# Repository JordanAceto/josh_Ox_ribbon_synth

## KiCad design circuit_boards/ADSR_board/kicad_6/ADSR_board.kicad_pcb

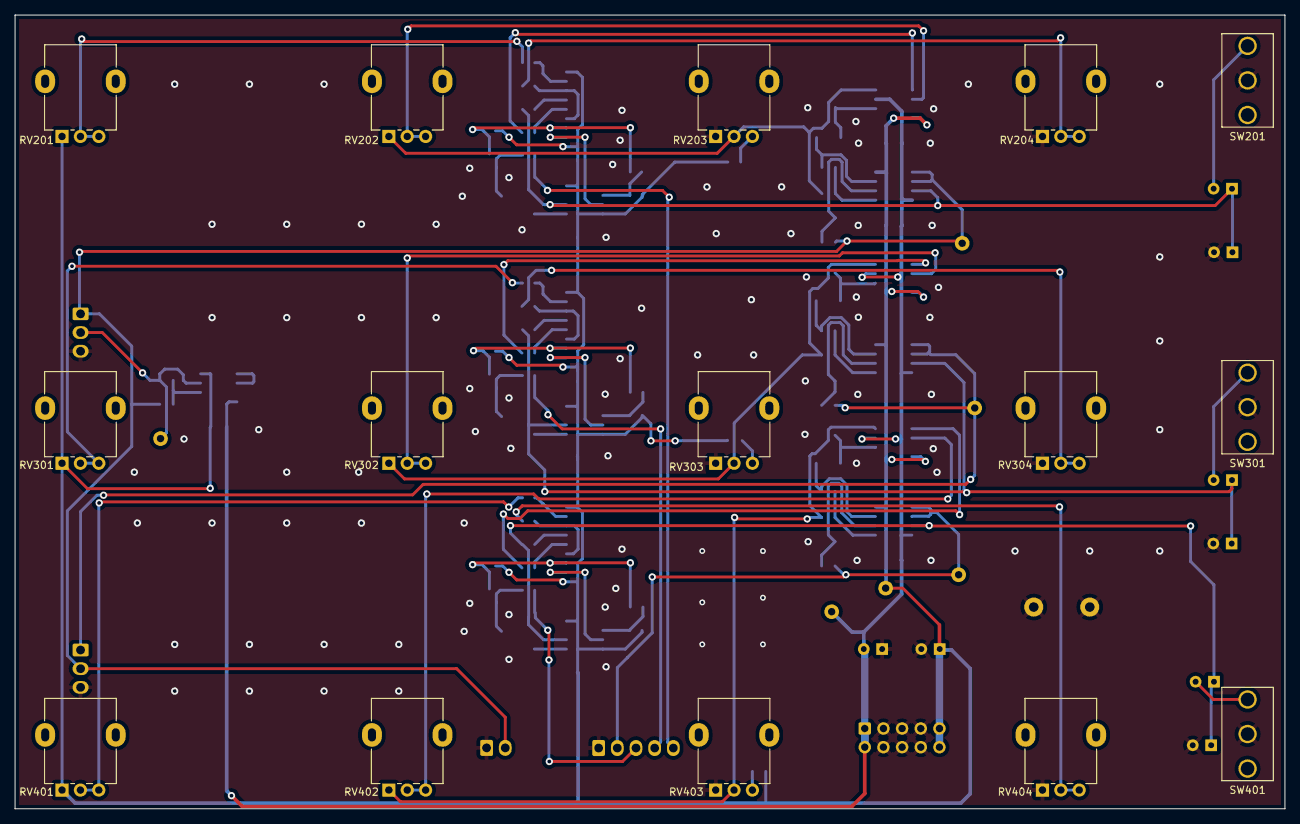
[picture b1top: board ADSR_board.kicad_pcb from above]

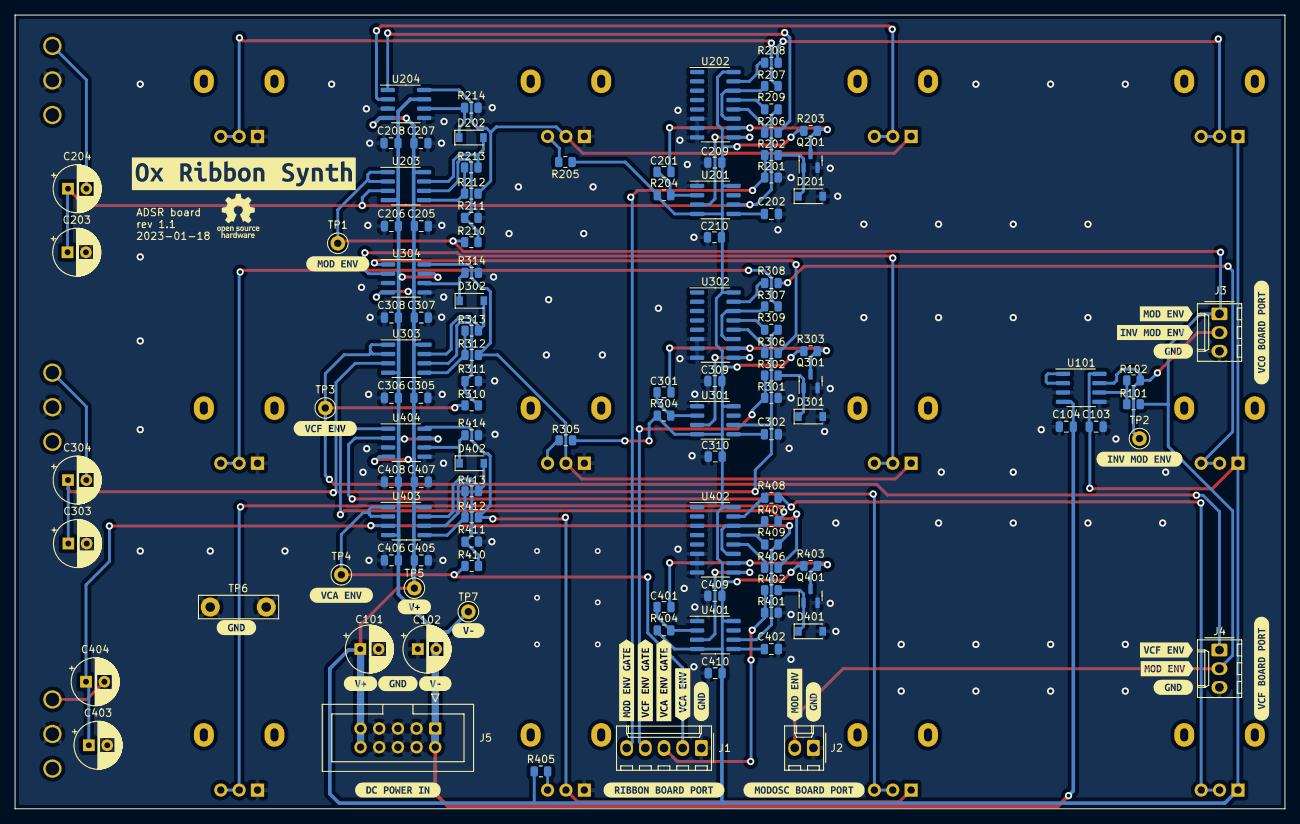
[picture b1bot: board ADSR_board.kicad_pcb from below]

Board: 2 copper layers, 172.7 x 107.9 mm, 156 parts (141 on the bottom side), 75 nets.

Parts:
C101, C102: 10u; CP_Radial_D6.3mm_P2.50mm
C103, C104, C205, C206, C207, C208, C209, C210, C305, C306, C307, C308, C309, C310, C405, C406, C407, C408, C409, C410: 100n; C_0805_2012Metric
C201, C202, C301, C302, C401, C402: 1n; C_0805_2012Metric
C203, C303, C403: 2u2; CP_Radial_D6.3mm_P2.50mm
C204, C304, C404: 22u; CP_Radial_D6.3mm_P2.50mm
D201, D202, D301, D302, D401, D402: 1N4148W; D_SOD-123
J1: ribbon_port; Molex_KK-254_AE-6410-05A_1x05_P2.54mm_Vertical
J2: modosc_port; Molex_KK-254_AE-6410-02A_1x02_P2.54mm_Vertical
J3: VCO_port; Molex_KK-254_AE-6410-03A_1x03_P2.54mm_Vertical
J4: VCF_port; Molex_KK-254_AE-6410-03A_1x03_P2.54mm_Vertical
J5: power_entry; IDC-Header_2x05_P2.54mm_Vertical
Q201, Q301, Q401: MMBT3904; SOT-23
R101, R102, R201, R202, R211, R301, R302, R311, R401, R402, R411: 100k; R_0805_2012Metric
R203, R204, R212, R214, R303, R304, R312, R314, R403, R404, R412, R414: 10k; R_0805_2012Metric
R205, R305, R405: 5k6; R_0805_2012Metric
R206, R207, R208, R306, R307, R308, R406, R407, R408: 22; R_0805_2012Metric
R209, R309, R409: 100; R_0805_2012Metric
R210, R310, R410: 2k7; R_0805_2012Metric
R213, R313, R413: 2M2; R_0805_2012Metric
RV201, RV202, RV204, RV301, RV302, RV304, RV401, RV402, RV404: 1MA; Potentiometer_Alpha_RD901F-40-00D_Single_Vertical
RV203, RV303, RV403: 10k; Potentiometer_Alpha_RD901F-40-00D_Single_Vertical
SW201, SW301, SW401: SW_SPDT; SPDT_mini_toggle
TP1: MOD env; TestPoint_Keystone_5000-5004_Miniature
TP2: inv mod env; TestPoint_Keystone_5000-5004_Miniature
TP3: VCF env; TestPoint_Keystone_5000-5004_Miniature
TP4: VCA env; TestPoint_Keystone_5000-5004_Miniature
TP5: V+; TestPoint_Keystone_5000-5004_Miniature
TP6: GND; TestPoint_Bridge_Pitch7.62mm_Drill1.3mm
TP7: V-; TestPoint_Keystone_5000-5004_Miniature
U101, U203, U303, U403: TL072; SOIC-8_3.9x4.9mm_P1.27mm
U201, U301, U401: TLC555; SOIC-8_3.9x4.9mm_P1.27mm
U202, U302, U402: CD4052B; SOIC-16_3.9x9.9mm_P1.27mm
U204, U304, U404: DG470EY; SOIC-8_3.9x4.9mm_P1.27mm
kibuzzard-62AC7A9F: G***; kibuzzard-62AC7A9F
kibuzzard-62AC77C9: G***; kibuzzard-62AC77C9
kibuzzard-62AC77E4: G***; kibuzzard-62AC77E4
kibuzzard-62AC77FB: G***; kibuzzard-62AC77FB
kibuzzard-62AC78CB: G***; kibuzzard-62AC78CB
kibuzzard-62AC79A3: G***; kibuzzard-62AC79A3
kibuzzard-62AC79C5: G***; kibuzzard-62AC79C5
kibuzzard-62AC755C, kibuzzard-62AC755C#2, kibuzzard-62AC755C#3, kibuzzard-62AC755C#4, kibuzzard-62AC755C#5, kibuzzard-62AC755C#6: G***; kibuzzard-62AC755C
kibuzzard-62AC758B, kibuzzard-62AC758B#2: G***; kibuzzard-62AC758B
kibuzzard-62AC762D: G***; kibuzzard-62AC762D
kibuzzard-62AC769B: G***; kibuzzard-62AC769B
kibuzzard-62AC791A, kibuzzard-62AC791A#2: G***; kibuzzard-62AC791A
kibuzzard-62AC792A, kibuzzard-62AC792A#2: G***; kibuzzard-62AC792A
kibuzzard-62AC7596: G***; kibuzzard-62AC7596
kibuzzard-62AC7711: G***; kibuzzard-62AC7711
kibuzzard-62AC7737: G***; kibuzzard-62AC7737
kibuzzard-62AC7758: G***; kibuzzard-62AC7758
kibuzzard-62AC7771: G***; kibuzzard-62AC7771
kibuzzard-62AC7810: G***; kibuzzard-62AC7810
kibuzzard-62AC7972: G***; kibuzzard-62AC7972
kibuzzard-62AC7989: G***; kibuzzard-62AC7989

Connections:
+15V: C101.1, C103.1, C205.1, C207.1, C209.1, C210.1, C305.1, C307.1, C309.1, C310.1, C405.1, C407.1, C409.1, C410.1, J5.9, J5.10, R203.1, R204.1, R205.1, R303.1, R304.1, R305.1, R403.1, R404.1, R405.1, RV201.1, RV301.1, RV401.1, TP5.1, U101.8 (V+), U201.4 (R), U201.8 (VCC), U202.16 (VDD), U203.8 (V+), U204.4 (V+), U301.4 (R), U301.8 (VCC), U302.16 (VDD), U303.8 (V+), U304.4 (V+), U401.4 (R), U401.8 (VCC), U402.16 (VDD), U403.8 (V+), U404.4 (V+)
-15V: C102.2, C104.2, C206.2, C208.2, C306.2, C308.2, C406.2, C408.2, J5.1, J5.2, TP7.1, U101.4 (V-), U203.4 (V-), U204.7 (V-), U303.4 (V-), U304.7 (V-), U403.4 (V-), U404.7 (V-)
/MOD_ENV_GATE: J1.5, R201.1, R202.1
/VCA_ADSR/OUT: J1.2, R410.2, TP4.1, U403.1, U403.2 (-)
/VCA_ENV_GATE: J1.3, R401.1, R402.1
/VCF_ADSR/OUT: J4.1, R310.2, TP3.1, U303.1, U303.2 (-)
/VCF_ENV_GATE: J1.4, R301.1, R302.1
/modulation_ADSR/OUT: J2.2, J3.1, J4.2, R101.1, R210.2, TP1.1, U203.1, U203.2 (-)
GND: C101.2, C102.1, C103.2, C104.1, C202.2, C203.2, C205.2, C206.1, C207.2, C208.1, C209.2, C210.2, C302.2, C303.2, C305.2, C306.1, C307.2, C308.1, C309.2, C310.2, C402.2, C403.2, C405.2, C406.1, C407.2, C408.1, C409.2, C410.2, D201.2 (A), D301.2 (A), D401.2 (A), J1.1, J2.1, J3.3, J4.3, J5.3, J5.4, J5.5, J5.6, J5.7, J5.8, Q201.2 (E), Q301.2 (E), Q401.2 (E), R201.2, R211.2, R214.2, R301.2, R311.2, R314.2, R401.2, R411.2, R414.2, RV203.1, RV204.1, RV303.1, RV304.1, RV403.1, RV404.1, SW201.2 (B), SW301.2 (B), SW401.2 (B), TP6.1, U101.3 (+), U101.5 (+), U201.1 (GND), U202.6 (INH), U202.7 (VEE), U202.8 (VSS), U204.3 (GND), U204.5 (~EN), U301.1 (GND), U302.6 (INH), U302.7 (VEE), U302.8 (VSS), U304.3 (GND), U304.5 (~EN), U401.1 (GND), U402.6 (INH), U402.7 (VEE), U402.8 (VSS), U404.3 (GND), U404.5 (~EN)
unnamed: C201.1, Q201.3 (C), R203.2, U202.10 (A)
unnamed: C201.2, R204.2, U201.2 (TR)
unnamed: C202.1, U201.5 (CV)
unnamed: C203.1, C204.1, R209.2, U201.6 (THR), U203.3 (+)
unnamed: C204.2, SW201.3 (C)
unnamed: C301.1, Q301.3 (C), R303.2, U302.10 (A)
unnamed: C301.2, R304.2, U301.2 (TR)
unnamed: C302.1, U301.5 (CV)
unnamed: C303.1, C304.1, R309.2, U301.6 (THR), U303.3 (+)
unnamed: C304.2, SW301.3 (C)
unnamed: C401.1, Q401.3 (C), R403.2, U402.10 (A)
unnamed: C401.2, R404.2, U401.2 (TR)
unnamed: C402.1, U401.5 (CV)
unnamed: C403.1, C404.1, R409.2, U401.6 (THR), U403.3 (+)
unnamed: C404.2, SW401.3 (C)
unnamed: D201.1 (K), Q201.1 (B), R202.2
unnamed: D202.1 (K), R214.1, U204.6
unnamed: D202.2 (A), R213.1, U203.7
unnamed: D301.1 (K), Q301.1 (B), R302.2
unnamed: D302.1 (K), R314.1, U304.6
unnamed: D302.2 (A), R313.1, U303.7
unnamed: D401.1 (K), Q401.1 (B), R402.2
unnamed: D402.1 (K), R414.1, U404.6
unnamed: D402.2 (A), R413.1, U403.7
unnamed: J3.2, R102.2, TP2.1, U101.7
unnamed: R101.2, R102.1, U101.6 (-)
unnamed: R205.2, RV203.3
unnamed: R206.1, U204.1
unnamed: R206.2, U202.12 (X0)
unnamed: R207.1, RV204.2, RV204.3
unnamed: R207.2, U202.11 (X3), U202.14 (X1)
unnamed: R208.1, U202.15 (X2)
unnamed: R208.2, RV201.2, RV201.3
unnamed: R209.1, U202.13 (X)
unnamed: R210.1, R211.1, U203.6 (-)
unnamed: R212.1, RV202.1, RV203.2, U204.8
unnamed: R212.2, R213.2, U203.5 (+)
unnamed: R305.2, RV303.3
unnamed: R306.1, U304.1
unnamed: R306.2, U302.12 (X0)
unnamed: R307.1, RV304.2, RV304.3
unnamed: R307.2, U302.11 (X3), U302.14 (X1)
unnamed: R308.1, U302.15 (X2)
unnamed: R308.2, RV301.2, RV301.3
unnamed: R309.1, U302.13 (X)
unnamed: R310.1, R311.1, U303.6 (-)
unnamed: R312.1, RV302.1, RV303.2, U304.8
unnamed: R312.2, R313.2, U303.5 (+)
unnamed: R405.2, RV403.3
unnamed: R406.1, U404.1
unnamed: R406.2, U402.12 (X0)
unnamed: R407.1, RV404.2, RV404.3
unnamed: R407.2, U402.11 (X3), U402.14 (X1)
unnamed: R408.1, U402.15 (X2)
unnamed: R408.2, RV401.2, RV401.3
unnamed: R409.1, U402.13 (X)
unnamed: R410.1, R411.1, U403.6 (-)
unnamed: R412.1, RV402.1, RV403.2, U404.8
unnamed: R412.2, R413.2, U403.5 (+)
unnamed: RV202.2, RV202.3, U204.2
unnamed: RV302.2, RV302.3, U304.2
unnamed: RV402.2, RV402.3, U404.2
unnamed: U101.1, U101.2 (-)
unnamed: U201.3 (Q), U202.9 (B)
unnamed: U301.3 (Q), U302.9 (B)
unnamed: U401.3 (Q), U402.9 (B)

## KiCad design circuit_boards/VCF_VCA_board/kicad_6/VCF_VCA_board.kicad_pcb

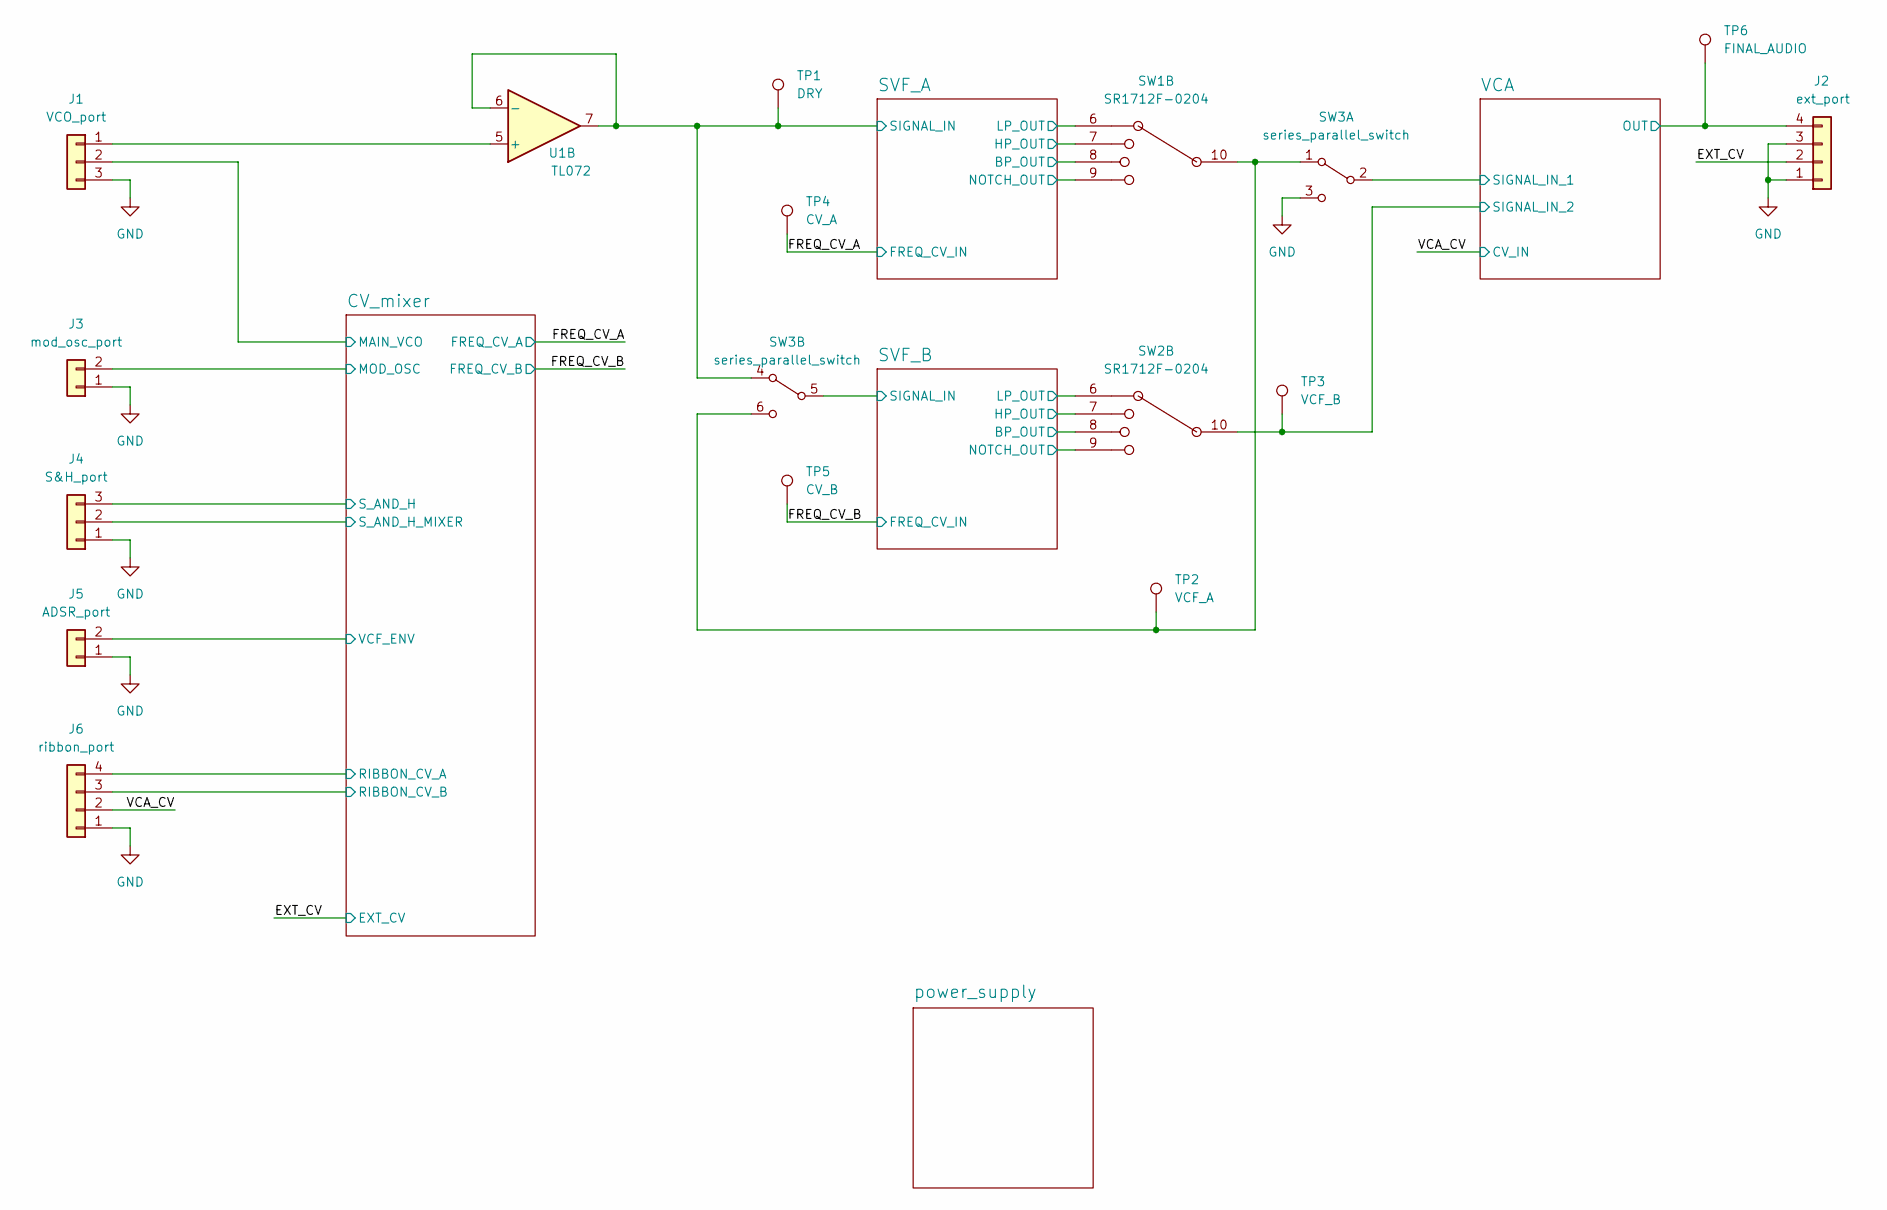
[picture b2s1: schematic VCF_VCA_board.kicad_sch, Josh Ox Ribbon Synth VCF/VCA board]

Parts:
J1: VCO_port; Molex_KK-254_AE-6410-03A_1x03_P2.54mm_Vertical
J2: ext_port; Molex_KK-254_AE-6410-04A_1x04_P2.54mm_Vertical
J3: mod_osc_port; Molex_KK-254_AE-6410-02A_1x02_P2.54mm_Vertical
J4: S&H_port; Molex_KK-254_AE-6410-03A_1x03_P2.54mm_Vertical
J5: ADSR_port; Molex_KK-254_AE-6410-02A_1x02_P2.54mm_Vertical
J6: ribbon_port; Molex_KK-254_AE-6410-04A_1x04_P2.54mm_Vertical
SW1, SW2: SR1712F-0204; SR1712F_rotary_switch
SW3: series_parallel_switch; DPDT_mini_toggle
TP1: DRY; TestPoint_Keystone_5000-5004_Miniature
TP2: VCF_A; TestPoint_Keystone_5000-5004_Miniature
TP3: VCF_B; TestPoint_Keystone_5000-5004_Miniature
TP4: CV_A; TestPoint_Keystone_5000-5004_Miniature
TP5: CV_B; TestPoint_Keystone_5000-5004_Miniature
TP6: FINAL_AUDIO; TestPoint_Keystone_5000-5004_Miniature
U1: TL072; SO-8_5.3x6.2mm_P1.27mm

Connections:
/CV_mixer/MAIN_VCO: J1.2; also elsewhere on the board
/CV_mixer/MOD_OSC: J3.2; also elsewhere on the board
/CV_mixer/RIBBON_CV_A: J6.4; also elsewhere on the board
/CV_mixer/RIBBON_CV_B: J6.3; also elsewhere on the board
/CV_mixer/S_AND_H: J4.3; also elsewhere on the board
/CV_mixer/S_AND_H_MIXER: J4.2; also elsewhere on the board
/CV_mixer/VCF_ENV: J5.2; also elsewhere on the board
/EXT_CV: J2.2; also elsewhere on the board
/FREQ_CV_A: TP4.1; also elsewhere on the board
/FREQ_CV_B: TP5.1; also elsewhere on the board
/SVF_A/BP_OUT: SW1.8; also elsewhere on the board
/SVF_A/HP_OUT: SW1.7; also elsewhere on the board
/SVF_A/LP_OUT: SW1.6; also elsewhere on the board
/SVF_A/NOTCH_OUT: SW1.9; also elsewhere on the board
/SVF_A/SIGNAL_IN: SW3.4 (A), TP1.1, U1.6 (-), U1.7; also elsewhere on the board
/SVF_B/BP_OUT: SW2.8; also elsewhere on the board
/SVF_B/HP_OUT: SW2.7; also elsewhere on the board
/SVF_B/LP_OUT: SW2.6; also elsewhere on the board
/SVF_B/NOTCH_OUT: SW2.9; also elsewhere on the board
/SVF_B/SIGNAL_IN: SW3.5 (B); also elsewhere on the board
/VCA/OUT: J2.4, TP6.1; also elsewhere on the board
/VCA/SIGNAL_IN_1: SW3.2 (B); also elsewhere on the board
/VCA/SIGNAL_IN_2: SW2.10, TP3.1; also elsewhere on the board
/VCA_CV: J6.2; also elsewhere on the board
unnamed: J1.1, U1.5 (+)
unnamed: SW1.10, SW3.1 (A), SW3.6 (C), TP2.1

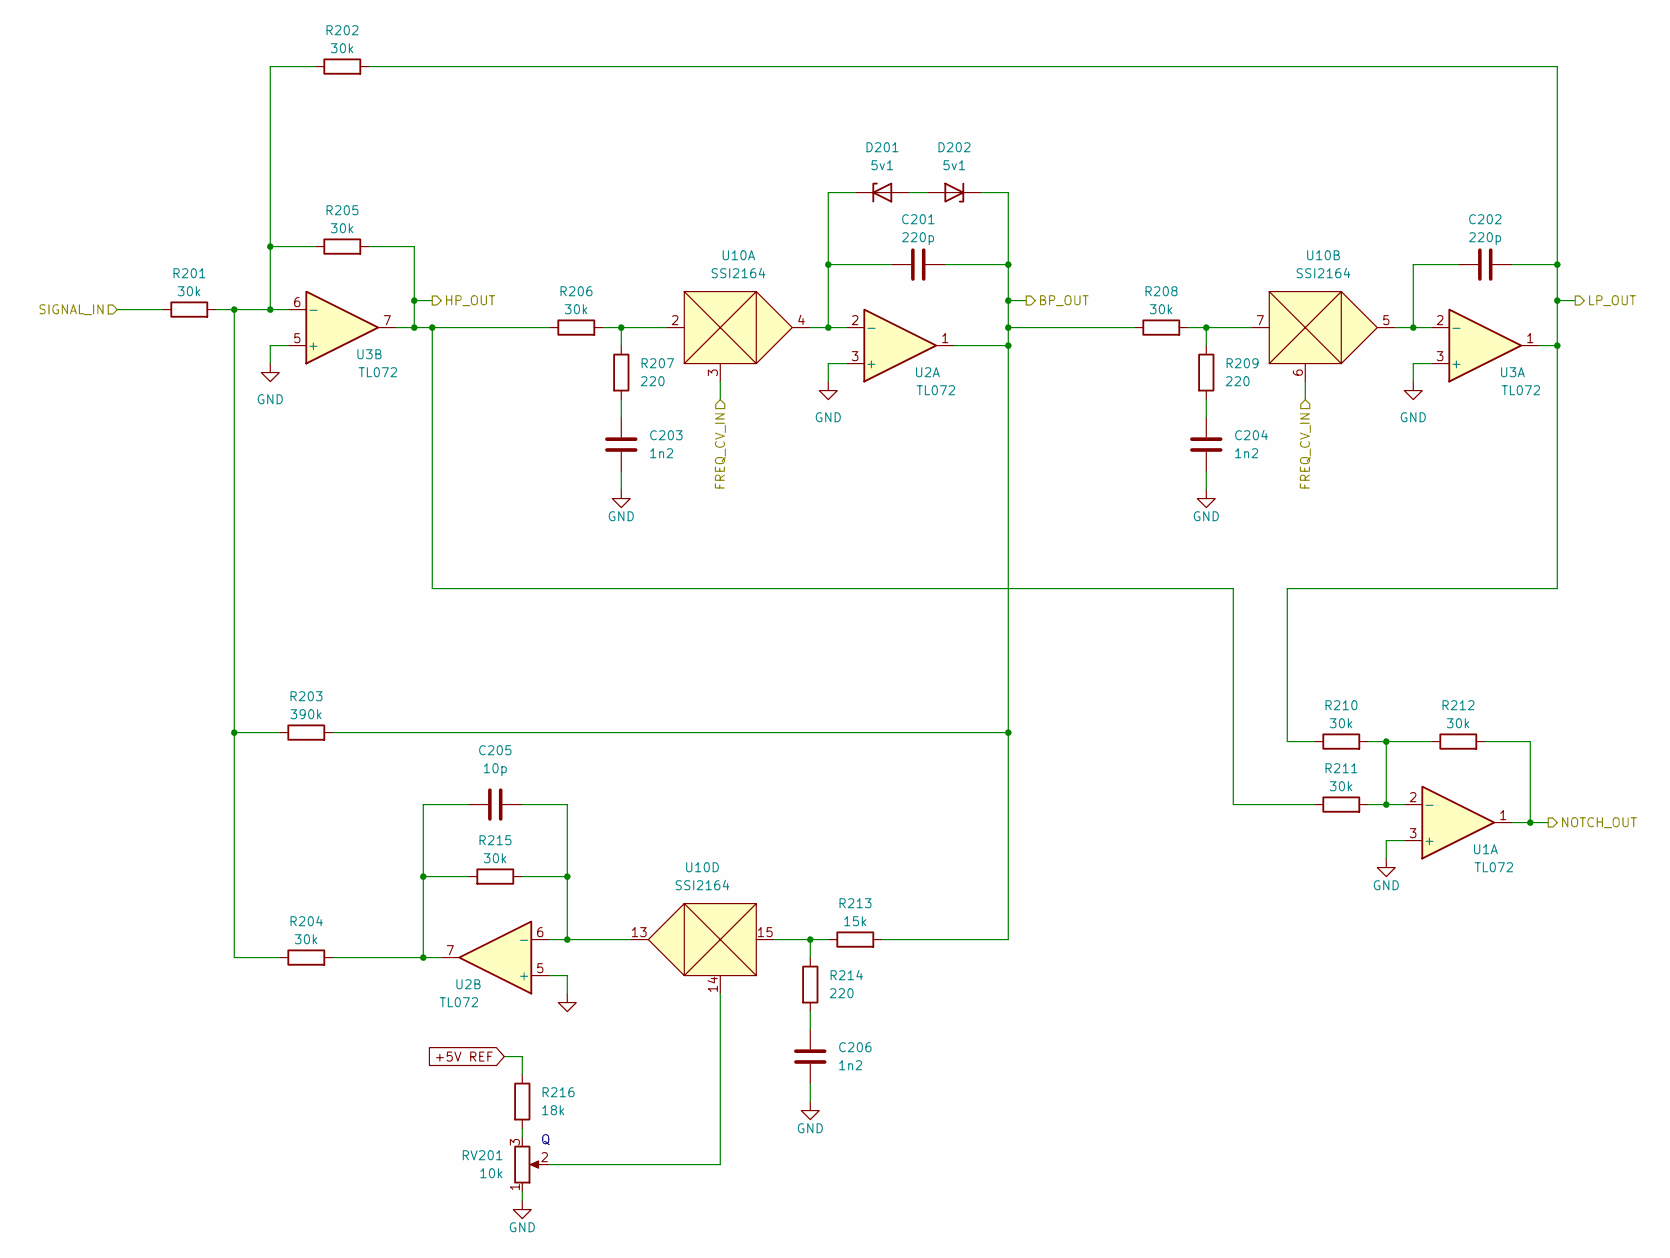
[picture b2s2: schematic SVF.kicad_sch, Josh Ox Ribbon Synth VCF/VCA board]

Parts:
C201, C202: 220p; C_Rect_L7.2mm_W4.5mm_P5.00mm_FKS2_FKP2_MKS2_MKP2
C203, C204, C206: 1n2; C_0805_2012Metric
C205: 10p; C_0805_2012Metric
D201, D202: 5v1; D_SOD-123
R201, R202, R204, R205, R206, R208, R210, R211, R212, R215: 30k; R_0805_2012Metric
R203: 390k; R_0805_2012Metric
R207, R209, R214: 220; R_0805_2012Metric
R213: 15k; R_0805_2012Metric
R216: 18k; R_0805_2012Metric
RV201: 10k; Potentiometer_Alpha_RD901F-40-00D_Single_Vertical
U1, U2, U3: TL072; SO-8_5.3x6.2mm_P1.27mm
U10: SSI2164; SOIC-16_3.9x9.9mm_P1.27mm

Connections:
+5V REF: R216.1; also elsewhere on the board
/FREQ_CV_A: U10.3, U10.6; also elsewhere on the board
/SVF_A/BP_OUT: C201.2, D202.1 (K), R203.2, R208.1, R213.2, U2.1; also elsewhere on the board
/SVF_A/HP_OUT: R205.2, R206.1, R211.1, U3.7; also elsewhere on the board
/SVF_A/LP_OUT: C202.2, R202.2, R210.1, U3.1; also elsewhere on the board
/SVF_A/NOTCH_OUT: R212.2, U1.1; also elsewhere on the board
/SVF_A/SIGNAL_IN: R201.1; also elsewhere on the board
unnamed: C201.1, D201.1 (K), U2.2 (-), U10.4
unnamed: C202.1, U3.2 (-), U10.5
unnamed: C203.1, R207.2
unnamed: C204.1, R209.2
unnamed: C205.1, R204.2, R215.2, U2.7
unnamed: C205.2, R215.1, U2.6 (-), U10.13
unnamed: C206.1, R214.2
unnamed: D201.2 (A), D202.2 (A)
unnamed: R201.2, R202.1, R203.1, R204.1, R205.1, U3.6 (-)
unnamed: R206.2, R207.1, U10.2
unnamed: R208.2, R209.1, U10.7
unnamed: R210.2, R211.2, R212.1, U1.2 (-)
unnamed: R213.1, R214.1, U10.15
unnamed: R216.2, RV201.3
unnamed: RV201.2, U10.14

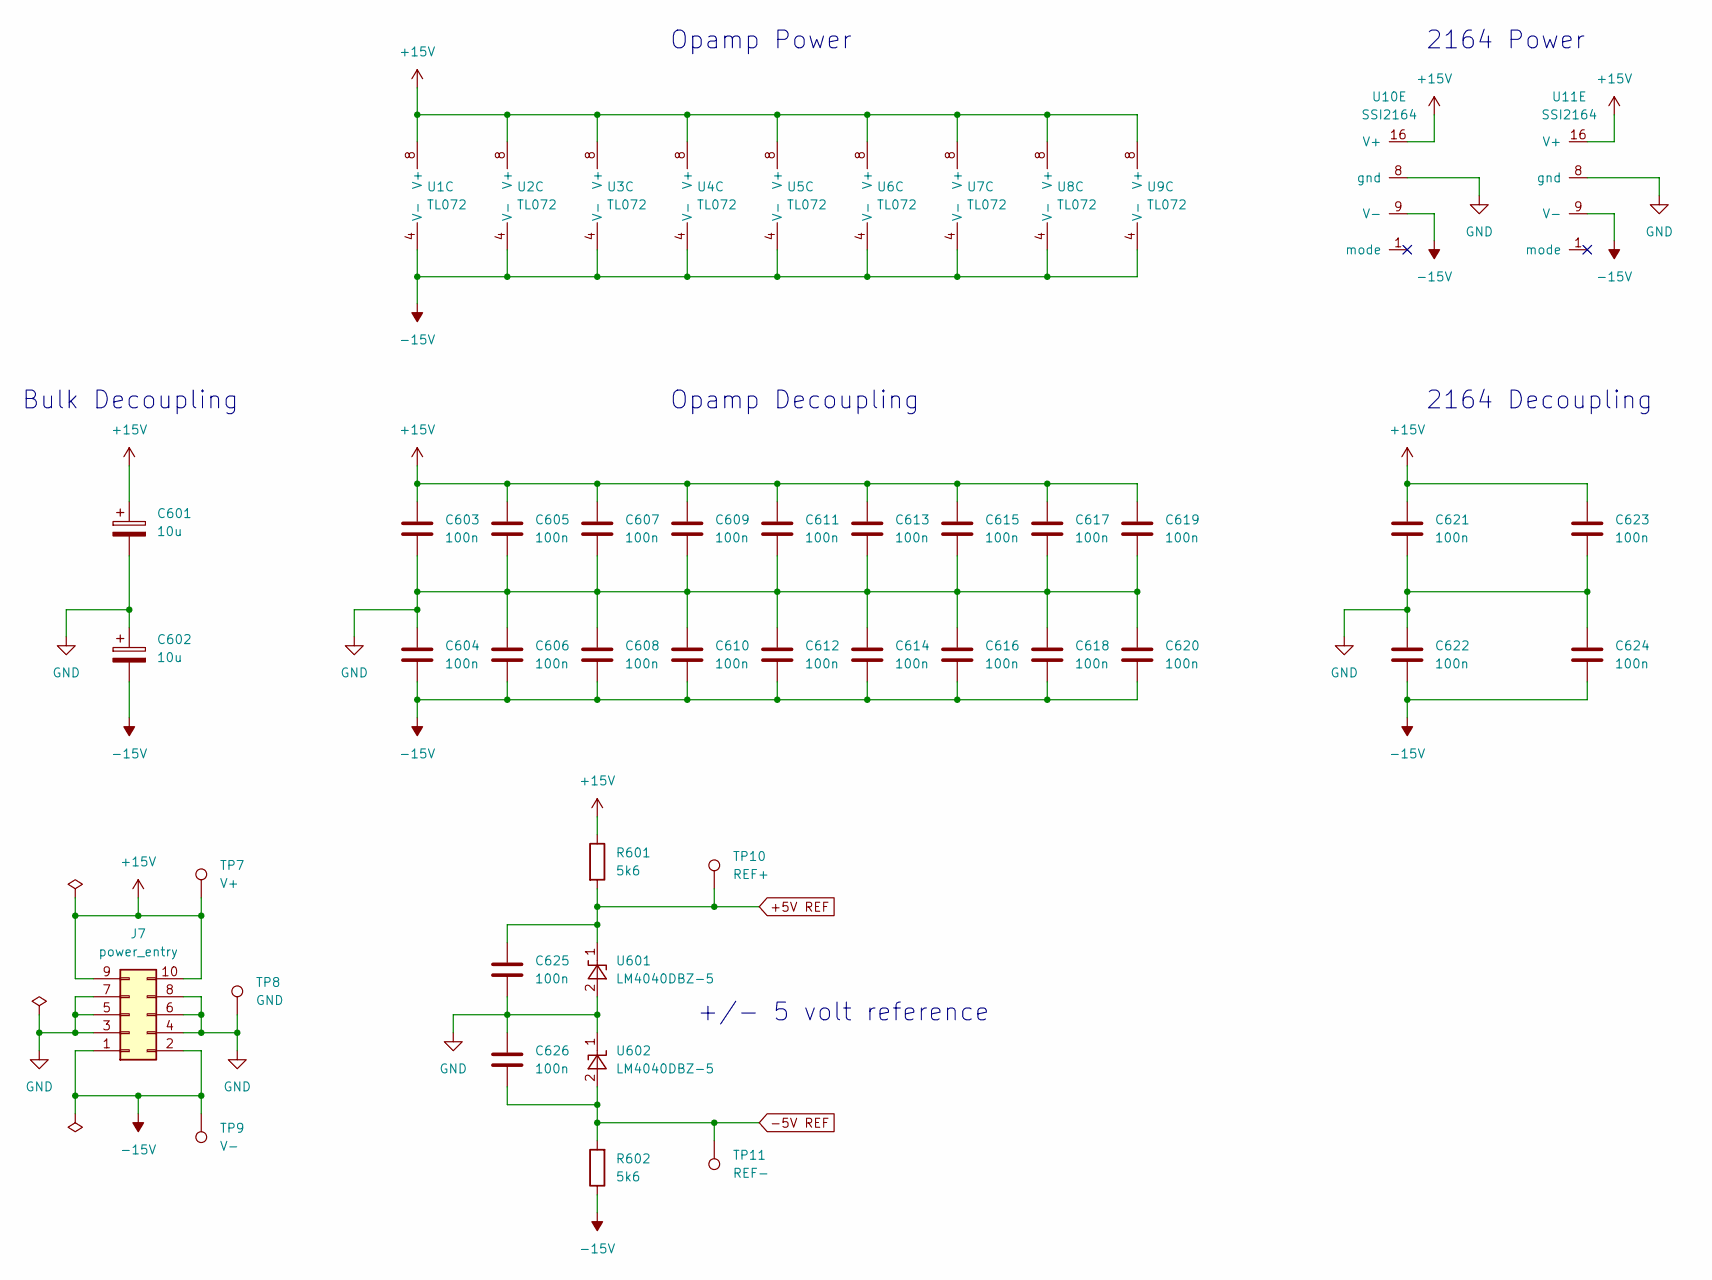
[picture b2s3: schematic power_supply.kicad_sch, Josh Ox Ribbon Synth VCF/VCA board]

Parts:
C601, C602: 10u; CP_Radial_D6.3mm_P2.50mm
C603, C604, C605, C606, C607, C608, C609, C610, C611, C612, C613, C614, C615, C616, C617, C618, C619, C620, C621, C622, C623, C624, C625, C626: 100n; C_0805_2012Metric
J7: power_entry; IDC-Header_2x05_P2.54mm_Vertical
R601, R602: 5k6; R_0805_2012Metric
TP7: V+; TestPoint_Keystone_5000-5004_Miniature
TP8: GND; TestPoint_Bridge_Pitch7.62mm_Drill1.3mm
TP9: V-; TestPoint_Keystone_5000-5004_Miniature
TP10: REF+; TestPoint_Keystone_5000-5004_Miniature
TP11: REF-; TestPoint_Keystone_5000-5004_Miniature
U1, U2, U3, U4, U5, U6, U7, U8, U9: TL072; SO-8_5.3x6.2mm_P1.27mm
U10, U11: SSI2164; SOIC-16_3.9x9.9mm_P1.27mm
U601, U602: LM4040DBZ-5; SOT-23

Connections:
+5V REF: C625.1, R601.2, TP10.1, U601.1 (K); also elsewhere on the board
+15V: C601.1, C603.1, C605.1, C607.1, C609.1, C611.1, C613.1, C615.1, C617.1, C619.1, C621.1, C623.1, J7.9, J7.10, R601.1, TP7.1, U1.8 (V+), U2.8 (V+), U3.8 (V+), U4.8 (V+), U5.8 (V+), U6.8 (V+), U7.8 (V+), U8.8 (V+), U9.8 (V+), U10.16 (V+), U11.16 (V+)
-5V REF: C626.1, R602.2, TP11.1, U602.2 (A); also elsewhere on the board
-15V: C602.2, C604.2, C606.2, C608.2, C610.2, C612.2, C614.2, C616.2, C618.2, C620.2, C622.2, C624.2, J7.1, J7.2, R602.1, TP9.1, U1.4 (V-), U2.4 (V-), U3.4 (V-), U4.4 (V-), U5.4 (V-), U6.4 (V-), U7.4 (V-), U8.4 (V-), U9.4 (V-), U10.9 (V-), U11.9 (V-)
/FREQ_CV_B: U11.3, U11.6; also elsewhere on the board
/SVF_B/BP_OUT: U4.1; also elsewhere on the board
/SVF_B/HP_OUT: U5.7; also elsewhere on the board
/SVF_B/LP_OUT: U5.1; also elsewhere on the board
/SVF_B/NOTCH_OUT: U6.7; also elsewhere on the board
unnamed 35: U4.2 (-), U11.4; also elsewhere on the board
unnamed 36: U5.2 (-), U11.5; also elsewhere on the board
unnamed 39: U4.7; also elsewhere on the board
unnamed 40: U4.6 (-), U11.13; also elsewhere on the board
unnamed 69: U5.6 (-); also elsewhere on the board
unnamed 70: U11.2; also elsewhere on the board
unnamed 71: U11.7; also elsewhere on the board
unnamed 72: U6.6 (-); also elsewhere on the board
unnamed 73: U11.15; also elsewhere on the board
unnamed 91: U11.14; also elsewhere on the board

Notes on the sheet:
Opamp Power
2164 Decoupling
+/- 5 volt reference
2164 Power
Bulk Decoupling
Opamp Decoupling

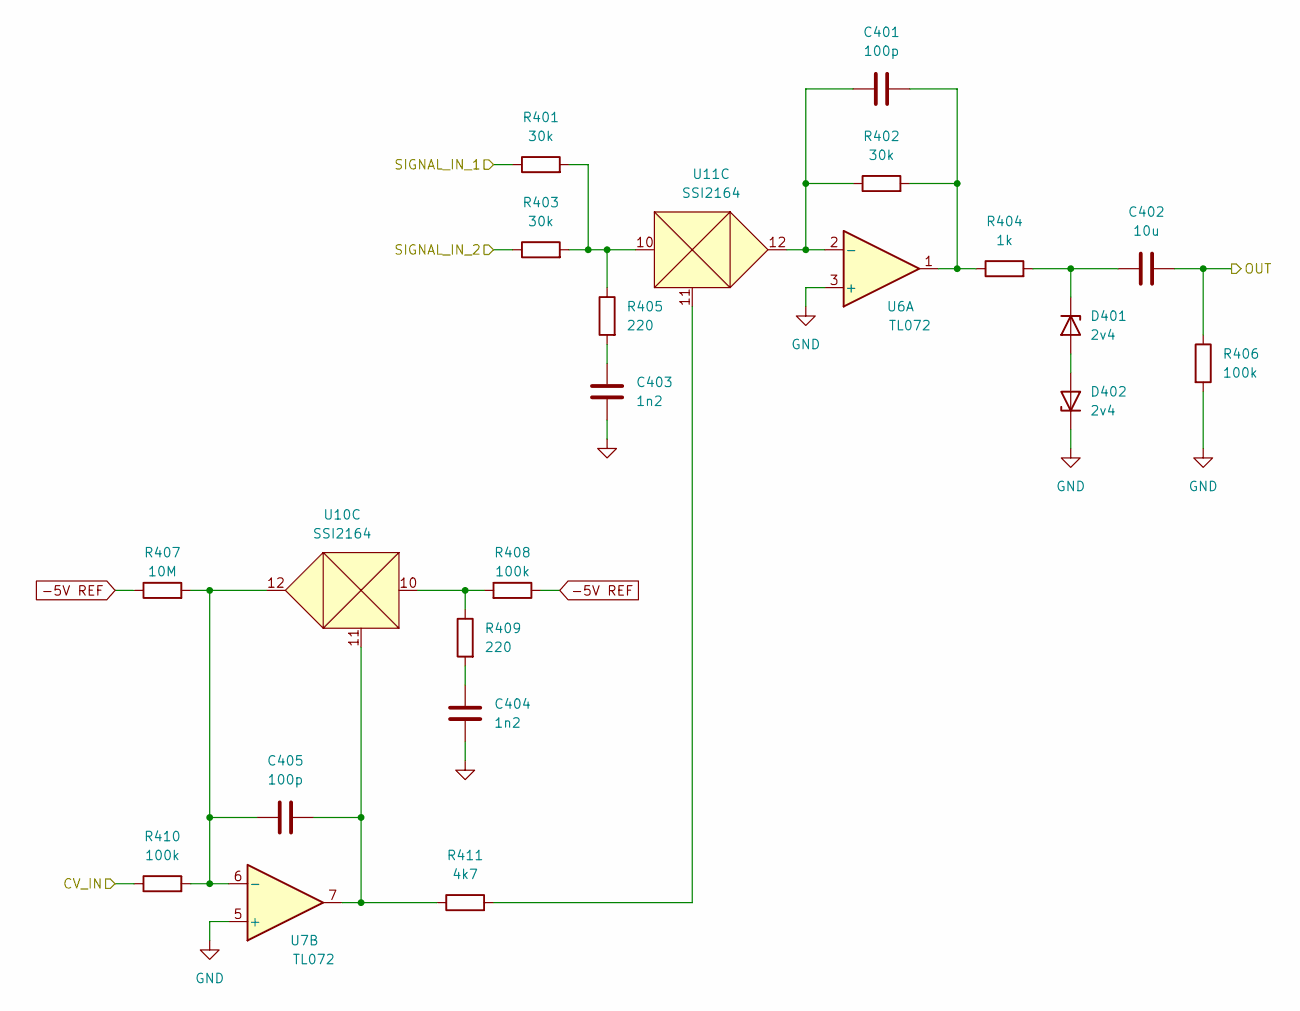
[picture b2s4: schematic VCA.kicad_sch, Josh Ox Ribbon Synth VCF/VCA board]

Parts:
C401, C405: 100p; C_0805_2012Metric
C402: 10u; C_Radial_D6.3mm_H5.0mm_P2.50mm
C403, C404: 1n2; C_0805_2012Metric
D401, D402: 2v4; D_SOD-123
R401, R402, R403: 30k; R_0805_2012Metric
R404: 1k; R_0805_2012Metric
R405, R409: 220; R_0805_2012Metric
R406, R408, R410: 100k; R_0805_2012Metric
R407: 10M; R_0805_2012Metric
R411: 4k7; R_0805_2012Metric
U6, U7: TL072; SO-8_5.3x6.2mm_P1.27mm
U10, U11: SSI2164; SOIC-16_3.9x9.9mm_P1.27mm

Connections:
-5V REF: R407.1, R408.1; also elsewhere on the board
/FREQ_CV_B: U11.3, U11.6; also elsewhere on the board
/SVF_B/NOTCH_OUT: U6.7; also elsewhere on the board
/VCA/OUT: C402.2, R406.1; also elsewhere on the board
/VCA/SIGNAL_IN_1: R401.1; also elsewhere on the board
/VCA/SIGNAL_IN_2: R403.1; also elsewhere on the board
/VCA_CV: R410.1; also elsewhere on the board
unnamed 35: U11.4; also elsewhere on the board
unnamed 36: U11.5; also elsewhere on the board
unnamed 40: U11.13; also elsewhere on the board
unnamed: C401.1, R402.1, U6.2 (-), U11.12
unnamed: C401.2, R402.2, R404.1, U6.1
unnamed: C402.1, D401.1 (K), R404.2
unnamed: C403.1, R405.2
unnamed: C404.1, R409.2
unnamed: C405.1, R407.2, R410.2, U7.6 (-), U10.12
unnamed: C405.2, R411.1, U7.7, U10.11
unnamed: D401.2 (A), D402.2 (A)
unnamed 70: U11.2; also elsewhere on the board
unnamed 71: U11.7; also elsewhere on the board
unnamed 72: U6.6 (-); also elsewhere on the board
unnamed 73: U11.15; also elsewhere on the board
unnamed: R401.2, R403.2, R405.1, U11.10
unnamed: R408.2, R409.1, U10.10
unnamed: R411.2, U11.11
unnamed 91: U11.14; also elsewhere on the board

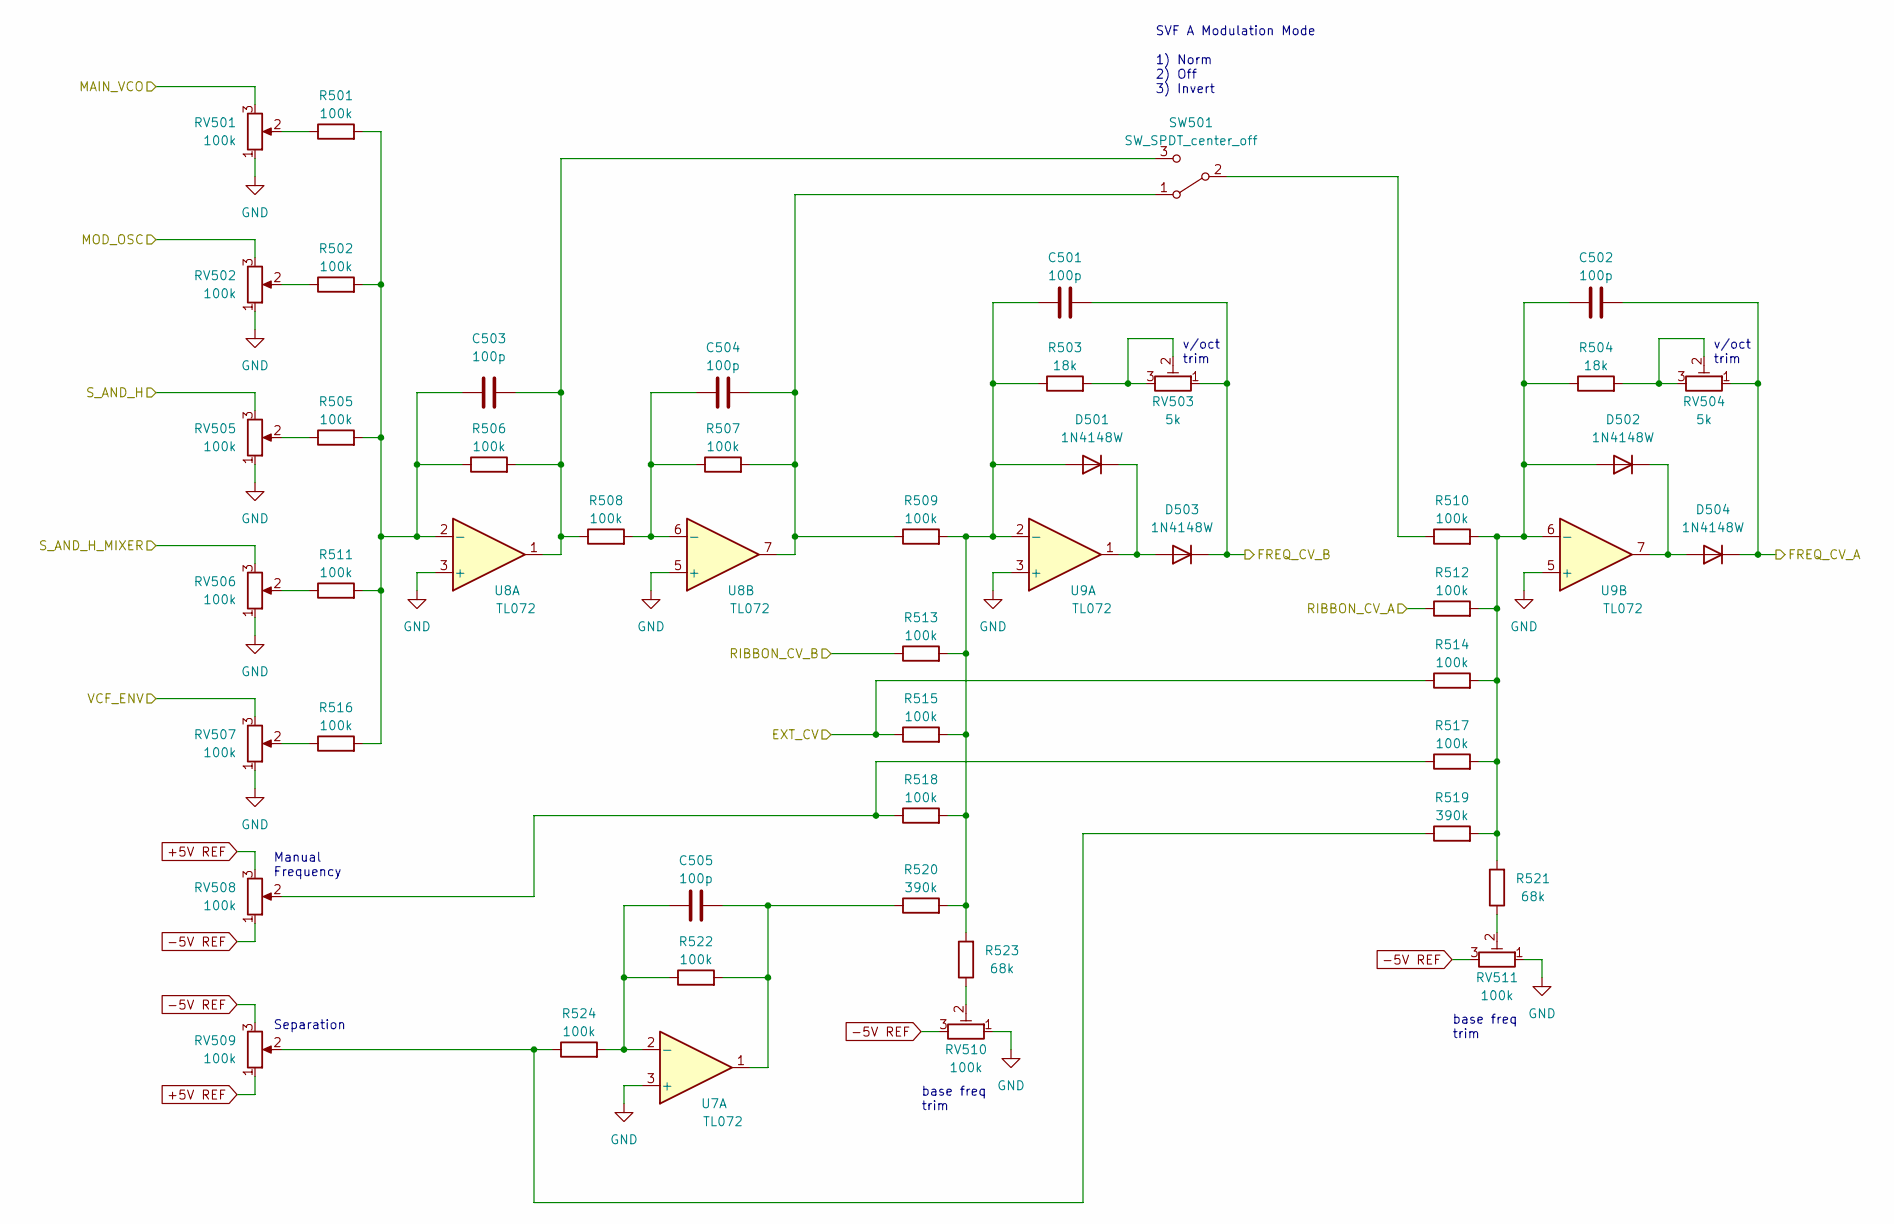
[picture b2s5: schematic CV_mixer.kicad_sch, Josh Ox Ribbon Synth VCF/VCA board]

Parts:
C501, C502, C503, C504, C505: 100p; C_0805_2012Metric
D501, D502, D503, D504: 1N4148W; D_SOD-123
R501, R502, R505, R506, R507, R508, R509, R510, R511, R512, R513, R514, R515, R516, R517, R518, R522, R524: 100k; R_0805_2012Metric
R503, R504: 18k; R_0805_2012Metric
R519, R520: 390k; R_0805_2012Metric
R521, R523: 68k; R_0805_2012Metric
RV501, RV502, RV505, RV506, RV507, RV508, RV509: 100k; Potentiometer_Alpha_RD901F-40-00D_Single_Vertical
RV503, RV504: 5k; Potentiometer_Bourns_3296W_Vertical
RV510, RV511: 100k; Potentiometer_Bourns_3296W_Vertical
SW501: SW_SPDT_center_off; SPDT_mini_toggle
U7, U8, U9: TL072; SO-8_5.3x6.2mm_P1.27mm

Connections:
+5V REF: RV508.3, RV509.1; also elsewhere on the board
-5V REF: RV508.1, RV509.3, RV510.3, RV511.3; also elsewhere on the board
/CV_mixer/MAIN_VCO: RV501.3; also elsewhere on the board
/CV_mixer/MOD_OSC: RV502.3; also elsewhere on the board
/CV_mixer/RIBBON_CV_A: R512.1; also elsewhere on the board
/CV_mixer/RIBBON_CV_B: R513.1; also elsewhere on the board
/CV_mixer/S_AND_H: RV505.3; also elsewhere on the board
/CV_mixer/S_AND_H_MIXER: RV506.3; also elsewhere on the board
/CV_mixer/VCF_ENV: RV507.3; also elsewhere on the board
/EXT_CV: R514.1, R515.1; also elsewhere on the board
/FREQ_CV_A: C502.2, D504.1 (K), RV504.1; also elsewhere on the board
/FREQ_CV_B: C501.2, D503.1 (K), RV503.1; also elsewhere on the board
unnamed: C501.1, D501.2 (A), R503.1, R509.2, R513.2, R515.2, R518.2, R520.2, R523.2, U9.2 (-)
unnamed: C502.1, D502.2 (A), R504.1, R510.2, R512.2, R514.2, R517.2, R519.2, R521.2, U9.6 (-)
unnamed: C503.1, R501.2, R502.2, R505.2, R506.1, R511.2, R516.2, U8.2 (-)
unnamed: C503.2, R506.2, R508.1, SW501.3 (C), U8.1
unnamed: C504.1, R507.1, R508.2, U8.6 (-)
unnamed: C504.2, R507.2, R509.1, SW501.1 (A), U8.7
unnamed: C505.1, R522.1, R524.2, U7.2 (-)
unnamed: C505.2, R520.1, R522.2, U7.1
unnamed: D501.1 (K), D503.2 (A), U9.1
unnamed: D502.1 (K), D504.2 (A), U9.7
unnamed: R501.1, RV501.2
unnamed: R502.1, RV502.2
unnamed: R503.2, RV503.2, RV503.3
unnamed: R504.2, RV504.2, RV504.3
unnamed: R505.1, RV505.2
unnamed: R510.1, SW501.2 (B)
unnamed: R511.1, RV506.2
unnamed: R516.1, RV507.2
unnamed: R517.1, R518.1, RV508.2
unnamed: R519.1, R524.1, RV509.2
unnamed: R521.1, RV511.2
unnamed: R523.1, RV510.2

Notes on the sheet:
Manual Frequency
SVF A Modulation Mode 1) Norm 2) Off 3) Invert
Separation
base freq trim
v/oct trim

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

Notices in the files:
circuit_boards/ADSR_board/kicad_6/ADSR_board.kicad_pcb:
creativecommons.org/licences/by/4.0
license: CC by 4.0
circuit_boards/VCF_VCA_board/kicad_6/CV_mixer.kicad_sch:
creativecommons.org/licenses/by/4.0
